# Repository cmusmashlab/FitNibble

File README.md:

# FitNibble
This is an open-source repo of the codes and hardware schematics used in the FitNibble paper:
FitNibble: A Field Study to Evaluate the Utility and Usability of Automatic Diet Monitoring in Food Journaling using an Eyeglasses-based Wearable

### This repo contains:
1. Firmware: which runs on a Rigado 350 nRf52 BLE module. This code is responsible for sensor data acquisition and feature extraction.
2. HW Schematics: for BLE module boards and the proximity sensor (VCLN4040) breakout board.
3. iOS App: used to communicate with the BLE module and the server running real-time ML classification.
4. ML Pipeline: the pipeline used to build DNN eating detection models.
5. Server script: running real-time activity classification and collecting app activity data. 
6. Sensor visualization: A Processing script for real-time sensing data visualization  + firmware streaming sensors' data via the serial UART protocol.

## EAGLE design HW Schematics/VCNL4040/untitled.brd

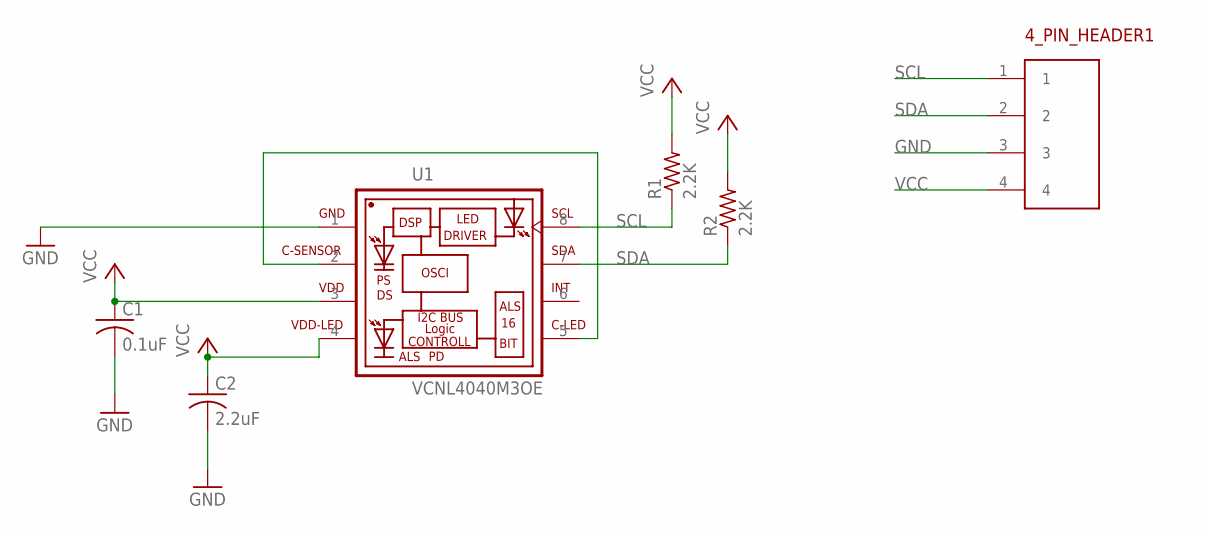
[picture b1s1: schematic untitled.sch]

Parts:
4_PIN_HEADER1: 4_PIN_HEADER
C1: 0.1uF; C0201
C2: 2.2uF; C0201
R1, R2: 2.2K; R0201
U1: VCNL4040M3OE; VISHAY_VCNL4040_4X2X1.1

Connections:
GND: 4_PIN_HEADER1.3, C1.2, C2.2, U1.1 (GND)
unnamed: U1.2 (C-SENSOR), U1.5 (C-LED)
SCL: 4_PIN_HEADER1.1, R1.1, U1.8 (SCL)
SDA: 4_PIN_HEADER1.2, R2.1, U1.7 (SDA)
VCC: 4_PIN_HEADER1.4, C1.1, C2.1, R1.2, R2.2, U1.3 (VDD), U1.4 (VDD-LED)

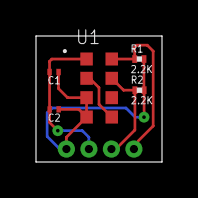
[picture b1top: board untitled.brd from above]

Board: 2 copper layers, 7.0 x 7.0 mm, 6 parts (0 on the bottom side), 5 nets.

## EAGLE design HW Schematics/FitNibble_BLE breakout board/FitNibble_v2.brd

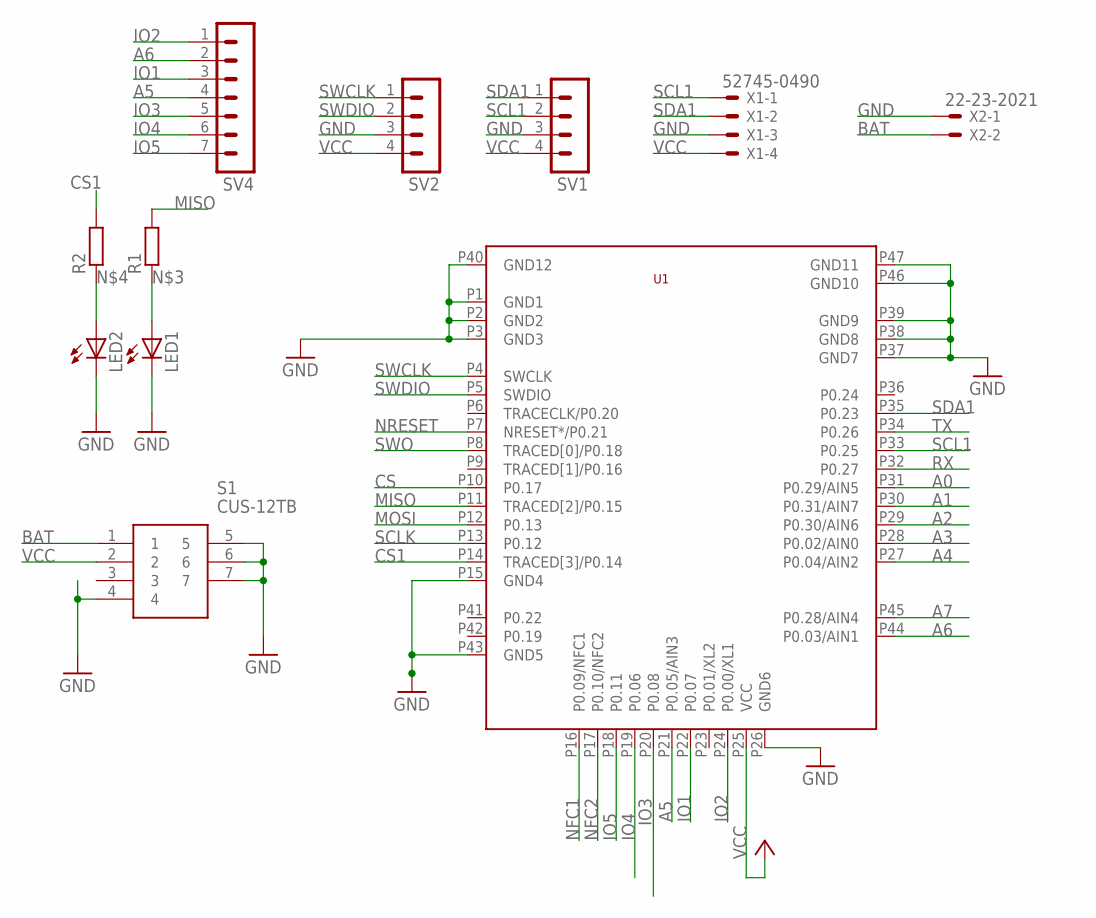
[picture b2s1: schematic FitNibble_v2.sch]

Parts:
LED1, LED2: LED_ESML0603; LED_SML0603
R1, R2: R-EU_R0603; R0603
S1: CUS-12TB; CUS-12B
SV1, SV2: MA04-1
SV4: MA07-1
U1: BMD-350
X1: 52745-0490
X2: 22-23-2021

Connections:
A0: U1.P31 (P0.29/AIN5)
A1: U1.P30 (P0.31/AIN7)
A2: U1.P29 (P0.30/AIN6)
A3: U1.P28 (P0.02/AIN0)
A4: U1.P27 (P0.04/AIN2)
A5: SV4.4, U1.P21 (P0.05/AIN3)
A6: SV4.2, U1.P44 (P0.03/AIN1)
A7: U1.P45 (P0.28/AIN4)
BAT: S1.1, X2.2
CS: U1.P10 (P0.17)
CS1: R2.2, U1.P14 (TRACED[3]/P0.14)
GND: LED1.C, LED2.C, S1.4, S1.5, S1.6, S1.7, SV1.3, SV2.3, U1.P1 (GND1), U1.P2 (GND2), U1.P3 (GND3), U1.P15 (GND4), U1.P26 (GND6), U1.P37 (GND7), U1.P38 (GND8), U1.P39 (GND9), U1.P40 (GND12), U1.P43 (GND5), U1.P46 (GND10), U1.P47 (GND11), X1.3, X2.1
IO1: SV4.3, U1.P22 (P0.07)
IO2: SV4.1, U1.P24 (P0.00/XL1)
IO3: SV4.5, U1.P20 (P0.08)
IO4: SV4.6, U1.P19 (P0.06)
IO5: SV4.7, U1.P18 (P0.11)
MISO: R1.2, U1.P11 (TRACED[2]/P0.15)
MOSI: U1.P12 (P0.13)
unnamed: LED1.A, R1.1
unnamed: LED2.A, R2.1
NFC1: U1.P16 (P0.09/NFC1)
NFC2: U1.P17 (P0.10/NFC2)
NRESET: U1.P7 (NRESET*/P0.21)
RX: U1.P32 (P0.27)
SCL1: SV1.2, U1.P33 (P0.25), X1.1
SCLK: U1.P13 (P0.12)
SDA1: SV1.1, U1.P35 (P0.23), X1.2
SWCLK: SV2.1, U1.P4 (SWCLK)
SWDIO: SV2.2, U1.P5 (SWDIO)
SWO: U1.P8 (TRACED[0]/P0.18)
TX: U1.P34 (P0.26)
VCC: S1.2, SV1.4, SV2.4, U1.P25 (VCC), X1.4

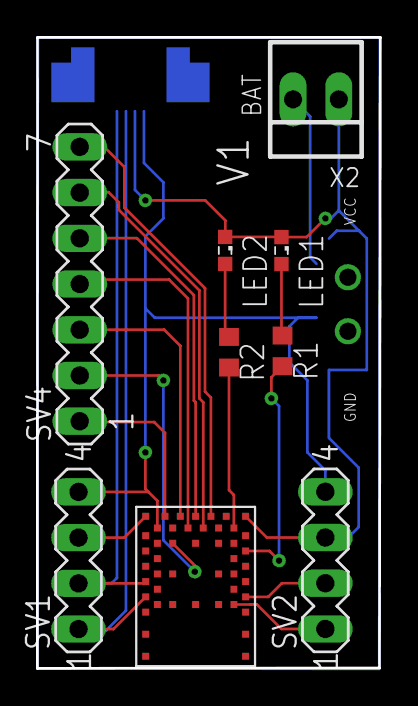
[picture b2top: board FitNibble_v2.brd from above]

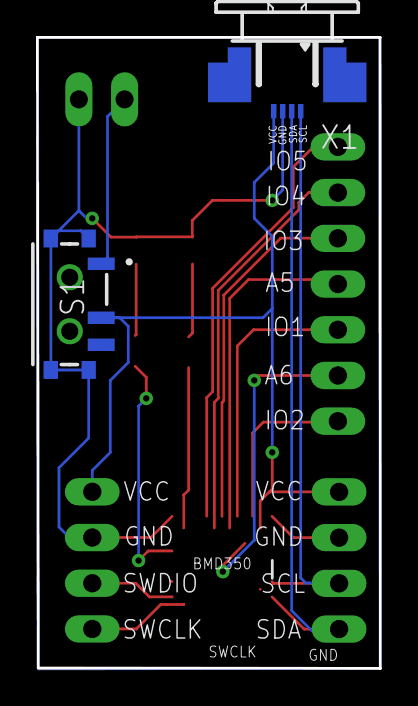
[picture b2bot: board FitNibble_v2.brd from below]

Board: 2 copper layers, 19.1 x 35.1 mm, 11 parts (2 on the bottom side), 18 nets.

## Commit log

2022-01-23 Uploading files
    Uploading codes and schematics and updating the README file
2022-01-23 Upload updated visualization codes
